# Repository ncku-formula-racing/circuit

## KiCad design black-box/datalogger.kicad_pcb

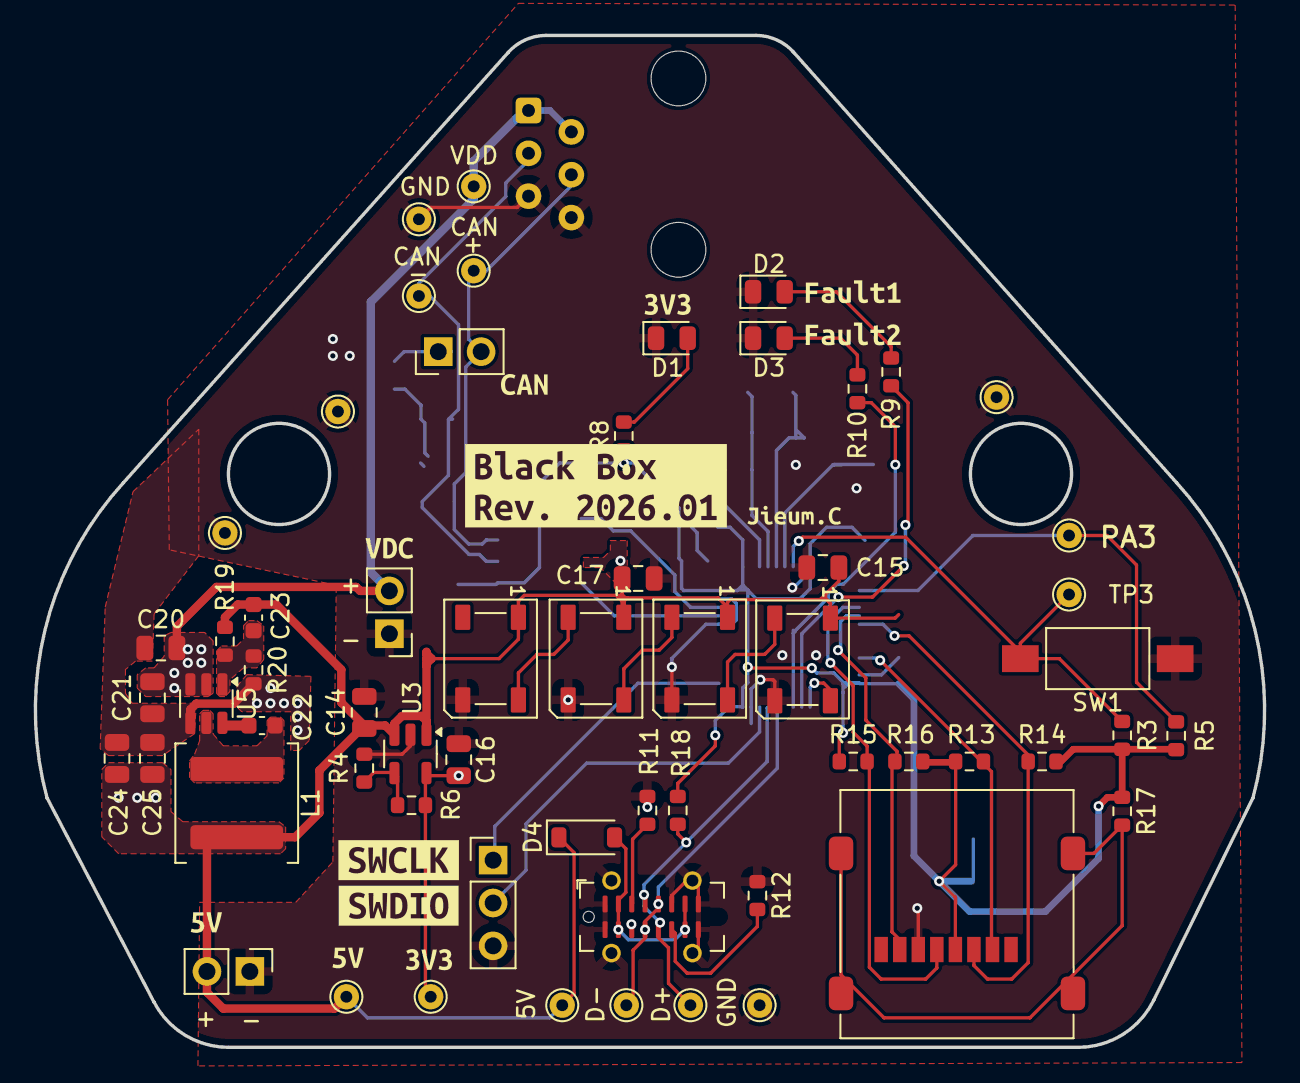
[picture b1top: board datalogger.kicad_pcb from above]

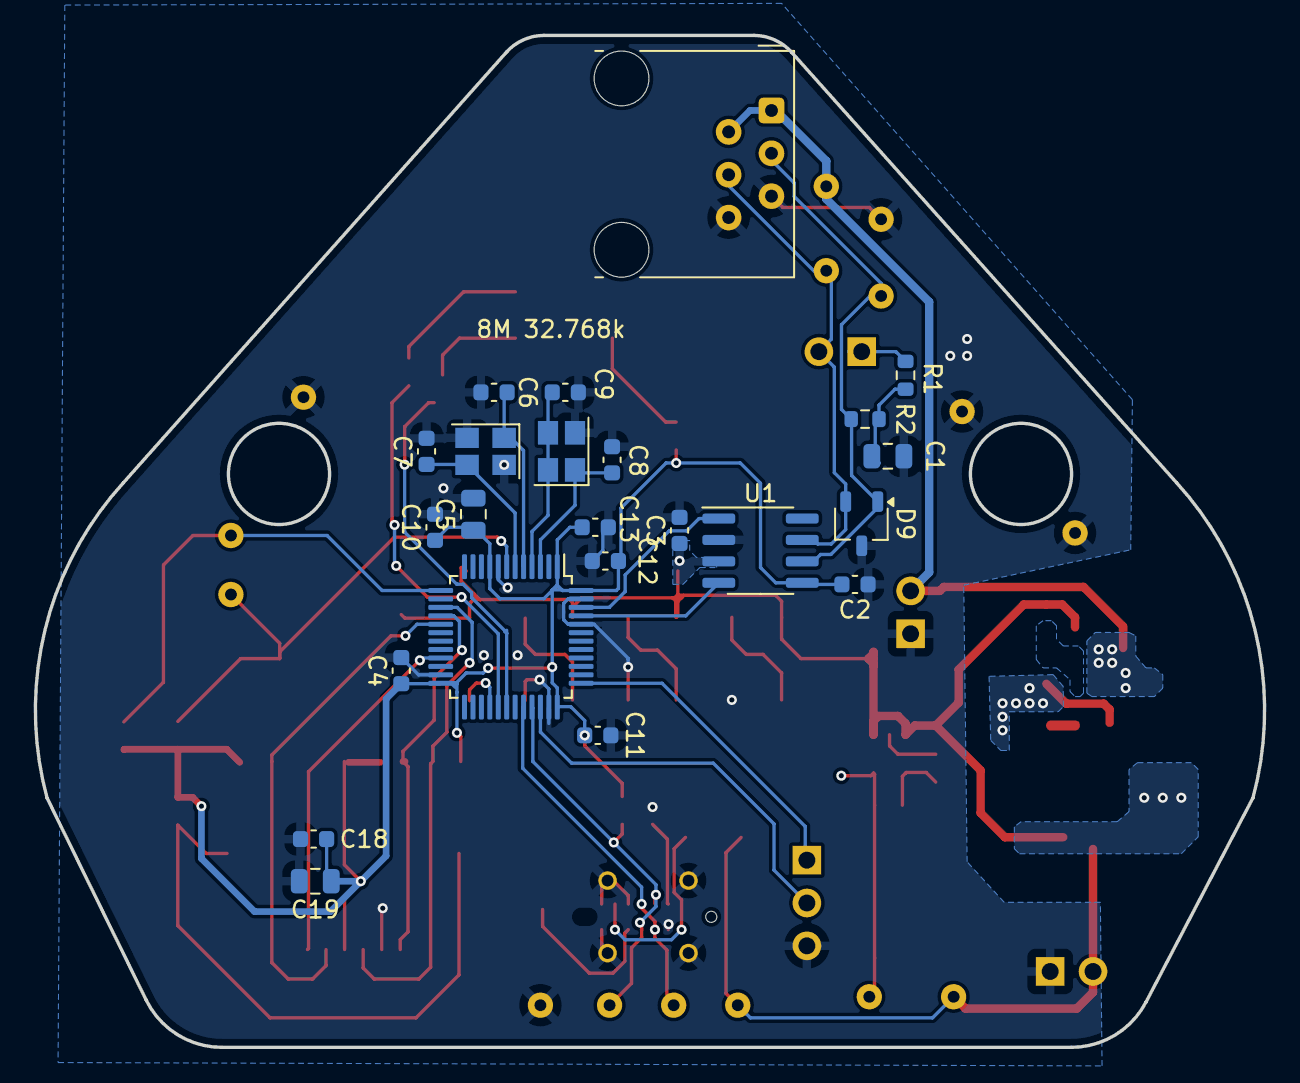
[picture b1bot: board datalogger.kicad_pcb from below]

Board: 2 copper layers, 72.9 x 60.0 mm, 95 parts (23 on the bottom side), 41 nets.

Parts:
5V1: USB_5V; TestPoint_THTPad_D1.5mm_Drill0.7mm
C1, C5, C14, C15, C17, C19: 1u; C_0805_2012Metric
C2, C3, C4, C10, C11, C12, C13, C18, C22: 100n; C_0603_1608Metric
C6, C7, C8, C9: 20p; C_0603_1608Metric
C16, C20, C21: 10u; C_0805_2012Metric
C23: 12p; C_0603_1608Metric
C24, C25: 22u; C_0805_2012Metric
CAN+1: CAN_P; TestPoint_THTPad_D1.5mm_Drill0.7mm
CAN-1: CAN_N; TestPoint_THTPad_D1.5mm_Drill0.7mm
D1, D2, D3: LED; LED_0805_2012Metric
D4: BAT46; D_SOD-123
D5, D6, D7, D8: WS2812B; LED_WS2812B_PLCC4_5.0x5.0mm_P3.2mm
D9: DESD2CAN2SOQ; TSOT-23
D+1: USB_D+; TestPoint_THTPad_D1.5mm_Drill0.7mm
D-1: USB_D-; TestPoint_THTPad_D1.5mm_Drill0.7mm
GND1: GND; TestPoint_THTPad_D1.5mm_Drill0.7mm
GND2: USB_gnd; TestPoint_THTPad_D1.5mm_Drill0.7mm
J1: RJ12; RJ12_Amphenol_54601-x06_Horizontal
J2: PROG; PinHeader_1x03_P2.54mm_Vertical
J3, J6: PWR; PinHeader_1x02_P2.54mm_Vertical
J4: Micro_SD_Card_Det1; microSD_HC_Molex_47219-2001
J5: USB_C_Receptacle_USB2.0_16P; USB_C_Receptacle_G-Switch_GT-USB-7051x
JP1: J_CAN; PinHeader_1x02_P2.54mm_Vertical
L1: 15uH; L_Coilcraft_XAL6060-XXX
R1, R2: 60; R_0603_1608Metric
R3, R5, R8, R9, R10, R13, R14, R15, R16, R17: 10k; R_0603_1608Metric
R4: 100k; R_0603_1608Metric
R6: 166k; R_0603_1608Metric
R11, R12: 5k1; R_0603_1608Metric
R18: 1.5k; R_0603_1608Metric
R19: 534k; R_0603_1608Metric
R20: 30k1; R_0603_1608Metric
SW1: SW_SPST; SW_SPST_FSMSM
TP1: TP_5V; TestPoint_THTPad_D1.5mm_Drill0.7mm
TP2: TP_3V3; TestPoint_THTPad_D1.5mm_Drill0.7mm
TP3: TestPoint; TestPoint_THTPad_D1.5mm_Drill0.7mm
TP11: Shutdown; TestPoint_THTPad_D1.5mm_Drill0.7mm
TP12, TP13, TP14: GND; TestPoint_THTPad_D1.5mm_Drill0.7mm
U1: SN65HVD256D; SOIC-8_3.9x4.9mm_P1.27mm
U2: STM32F103C8Tx; LQFP-48_7x7mm_P0.5mm
U3: AP2204K-ADJ; SOT-23-5
U5: AP63200WU; TSOT-23-6
VDC1: VDD; TestPoint_THTPad_D1.5mm_Drill0.7mm
Y1: 8M; Crystal_SMD_SeikoEpson_FA238-4Pin_3.2x2.5mm
Y2: 32.768k; Crystal_SMD_SeikoEpson_FA238-4Pin_3.2x2.5mm
kibuzzard-6952B1CA: G***; kibuzzard-6952B1CA
kibuzzard-6952B3A2: G***; kibuzzard-6952B3A2
kibuzzard-6952B3D6: G***; kibuzzard-6952B3D6
kibuzzard-6952B4C2: G***; kibuzzard-6952B4C2
kibuzzard-6952B5C0: G***; kibuzzard-6952B5C0
kibuzzard-6952B12B: G***; kibuzzard-6952B12B
kibuzzard-6952B13F: G***; kibuzzard-6952B13F
kibuzzard-6952B17D, kibuzzard-6952B17D#2: G***; kibuzzard-6952B17D
kibuzzard-6952B165, kibuzzard-6952B165#2: G***; kibuzzard-6952B165
kibuzzard-6977A83C: G***; kibuzzard-6977A83C

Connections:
+3V3: C2.1, C4.1, C5.1, C10.1, C11.1, C12.1, C13.1, C16.1, C18.1, C19.1, J4.4 (VDD), R3.1, R5.1, R6.1, R8.1, R13.1, R14.1, R15.1, R16.1, R17.1, R18.1, TP2.1, U1.5 (VRXD), U2.1 (VBAT), U2.9 (VDDA), U2.24 (VDD), U2.36 (VDD), U2.48 (VDD), U3.5 (VOUT)
+5V: 5V1.1, C3.1, C14.1, C15.1, C17.1, C23.1, C24.1, C25.1, D4.1 (K), D5.1 (VDD), D6.1 (VDD), D7.1 (VDD), D8.1 (VDD), J6.2, L1.2, R19.1, TP1.1, U1.3 (VCC), U3.1 (VIN), U3.3 (EN)
/LSE_IN: C8.1, U2.3 (PC14), Y2.1
/LSE_OUT: C9.1, U2.4 (PC15), Y2.3, Y2.4
/RCC_OSC_IN: C6.1, U2.5 (PD0), Y1.1
/RCC_OSC_OUT: C7.1, U2.6 (PD1), Y1.3
CAN_N: CAN-1.1, D9.1 (A1), J1.3, R2.2, U1.6 (CANL)
CAN_P: CAN+1.1, D9.2 (A2), J1.4, JP1.2 (B), U1.7 (CANH)
CRX: U1.4 (RXD), U2.45 (PB8)
CTX: U1.1 (TXD), U2.46 (PB9)
D+: D+1.1, J5.A6 (D+), J5.B6 (D+), R18.2, U2.33 (PA12)
D-: D-1.1, J5.A7 (D-), J5.B7 (D-), U2.32 (PA11)
GND: C1.2, C2.2, C3.2, C4.2, C5.2, C6.2, C7.2, C8.2, C9.2, C10.2, C11.2, C12.2, C13.2, C14.2, C15.2, C16.2, C17.2, C18.2, C19.2, C20.2, C21.2, C24.2, C25.2, D1.1 (K), D2.1 (K), D3.1 (K), D5.3 (VSS), D6.3 (VSS), D7.3 (VSS), D8.3 (VSS), D9.3 (common), GND1.1, GND2.1, J1.5, J1.6, J2.3, J3.1, J4.6 (VSS), J5.A1 (GND), J5.A8 (SBU1), J5.A12 (GND), J5.B1 (GND), J5.B8 (SBU2), J5.B12 (GND), J5.S1 (SHIELD), J6.1, R4.1, R11.1, R12.1, R20.2, SW1.1 (A), TP12.1, TP13.1, TP14.1, U1.2 (GND), U2.8 (VSSA), U2.23 (VSS), U2.35 (VSS), U2.44 (BOOT0), U2.47 (VSS), U3.2 (GND), U5.4 (GND), Y1.2, Y1.4, Y2.2
LED1: R9.1, U2.29 (PA8)
LED2: R10.1, U2.30 (PA9)
NRST: R3.2, SW1.2 (B), TP3.1, U2.7 (NRST)
unnamed: C1.1, R1.2, R2.1
unnamed: D1.2 (A), R8.2
unnamed: D2.2 (A), R9.2
unnamed: D3.2 (A), R10.2
unnamed: D4.2 (A), J5.A4 (VBUS), J5.A9 (VBUS), J5.B4 (VBUS), J5.B9 (VBUS)
unnamed: D5.2 (DOUT), D6.4 (DIN)
unnamed: D6.2 (DOUT), D7.4 (DIN)
unnamed: D7.2 (DOUT), D8.4 (DIN)
unnamed: J4.9 (DET), R17.2
unnamed: J5.A5 (CC1), R11.2
unnamed: J5.B5 (CC2), R12.2
unnamed: JP1.1 (A), R1.1
unnamed: R4.2, R6.2, U3.4 (ADJ)
unnamed: C22.2, U5.6 (BST)
unnamed: C23.2, R19.2, R20.1, U5.1 (FB)
unnamed: C22.1, L1.1, U5.5 (SW)
RGB: D5.4 (DIN), U2.28 (PB15)
SD_CS: J4.2 (DAT3/CD), R13.2, U2.21 (PB10)
SPI1_MISO: J4.7 (DAT0), R16.2, U2.16 (PA6)
SPI1_MOSI: J4.3 (CMD), R14.2, U2.17 (PA7)
SPI1_SCK: J4.5 (CLK), R15.2, U2.15 (PA5)
SWCLK: J2.1, U2.37 (PA14)
SWDIO: J2.2, U2.34 (PA13)
Shutdown: R5.2, TP11.1, U2.13 (PA3)
VDC: C20.1, C21.1, J1.1, J1.2, J3.2, U5.2 (EN), U5.3 (IN), VDC1.1

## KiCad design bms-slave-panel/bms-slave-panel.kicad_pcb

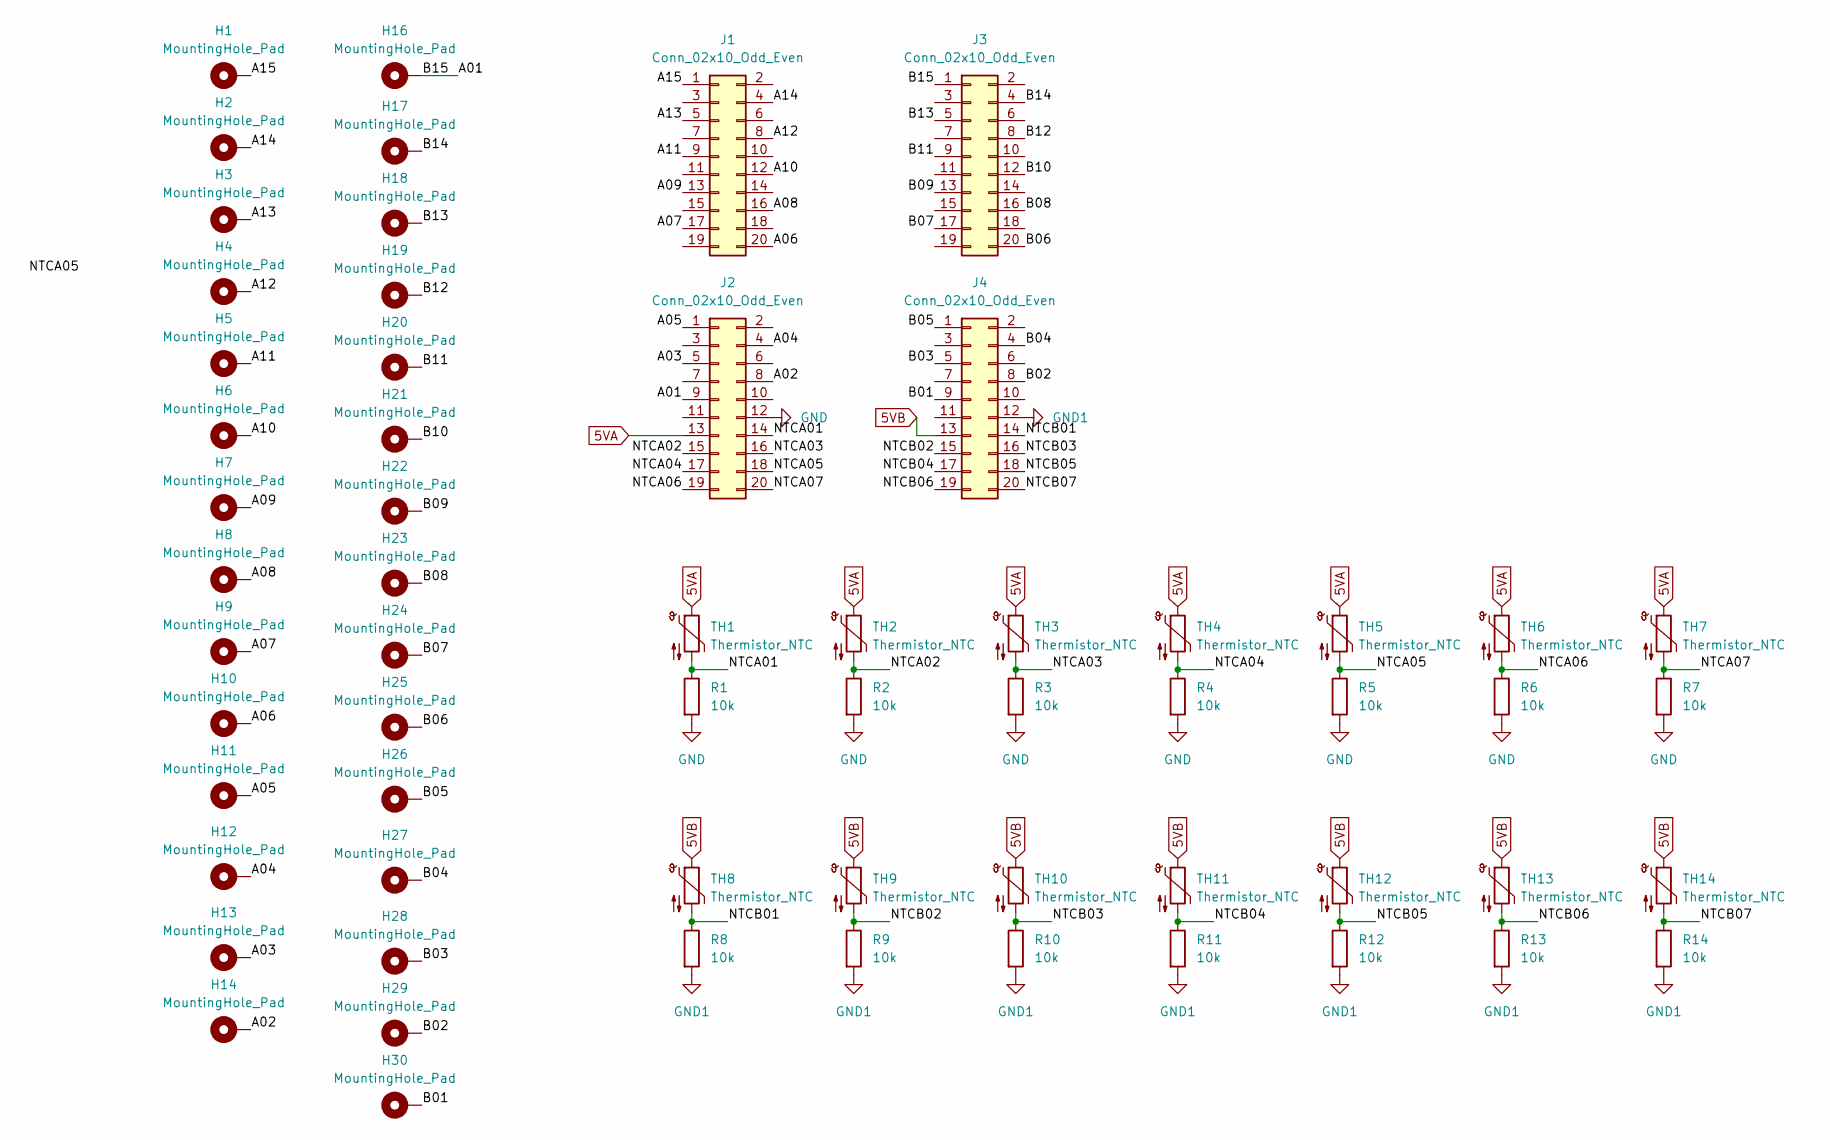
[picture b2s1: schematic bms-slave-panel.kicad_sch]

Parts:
H1, H2, H3, H4, H5, H6, H7, H8, H9, H10, H11, H12, H13, H14, H16, H17, H18, H19, H20, H21, H22, H23, H24, H25, H26, H27, H28, H29, H30: MountingHole_Pad; MountingHole_4.3mm_M4_DIN965_Pad
J1, J2, J3, J4: Conn_02x10_Odd_Even; PinHeader_2x10_P2.54mm_Vertical_SMD
R1, R2, R3, R4, R5, R6, R7, R8, R9, R10, R11, R12, R13, R14: 10k; R_0805_2012Metric
TH1, TH2, TH3, TH4, TH5, TH6, TH7, TH8, TH9, TH10, TH11, TH12, TH13, TH14: Thermistor_NTC; R_0805_2012Metric

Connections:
5VA: J2.13, TH1.1, TH2.1, TH3.1, TH4.1, TH5.1, TH6.1, TH7.1
5VB: J4.13, TH8.1, TH9.1, TH10.1, TH11.1, TH12.1, TH13.1, TH14.1
/A01: H16.1, J2.9, J3.1
/A02: H14.1, J2.8
/A03: H13.1, J2.5
/A04: H12.1, J2.4
/A05: H11.1, J2.1
/A06: H10.1, J1.20
/A07: H9.1, J1.17
/A08: H8.1, J1.16
/A09: H7.1, J1.13
/A10: H6.1, J1.12
/A11: H5.1, J1.9
/A12: H4.1, J1.8
/A13: H3.1, J1.5
/A14: H2.1, J1.4
/A15: H1.1, J1.1
/B01: H30.1, J4.9
/B02: H29.1, J4.8
/B03: H28.1, J4.5
/B04: H27.1, J4.4
/B05: H26.1, J4.1
/B06: H25.1, J3.20
/B07: H24.1, J3.17
/B08: H23.1, J3.16
/B09: H22.1, J3.13
/B10: H21.1, J3.12
/B11: H20.1, J3.9
/B12: H19.1, J3.8
/B13: H18.1, J3.5
/B14: H17.1, J3.4
/NTCA01: J2.14, R1.1, TH1.2
/NTCA02: J2.15, R2.1, TH2.2
/NTCA03: J2.16, R3.1, TH3.2
/NTCA04: J2.17, R4.1, TH4.2
/NTCA05: J2.18, R5.1, TH5.2
/NTCA06: J2.19, R6.1, TH6.2
/NTCA07: J2.20, R7.1, TH7.2
/NTCB01: J4.14, R8.1, TH8.2
/NTCB02: J4.15, R9.1, TH9.2
/NTCB03: J4.16, R10.1, TH10.2
/NTCB04: J4.17, R11.1, TH11.2
/NTCB05: J4.18, R12.1, TH12.2
/NTCB06: J4.19, R13.1, TH13.2
/NTCB07: J4.20, R14.1, TH14.2
GND: J2.12, R1.2, R2.2, R3.2, R4.2, R5.2, R6.2, R7.2
GND1: J4.12, R8.2, R9.2, R10.2, R11.2, R12.2, R13.2, R14.2

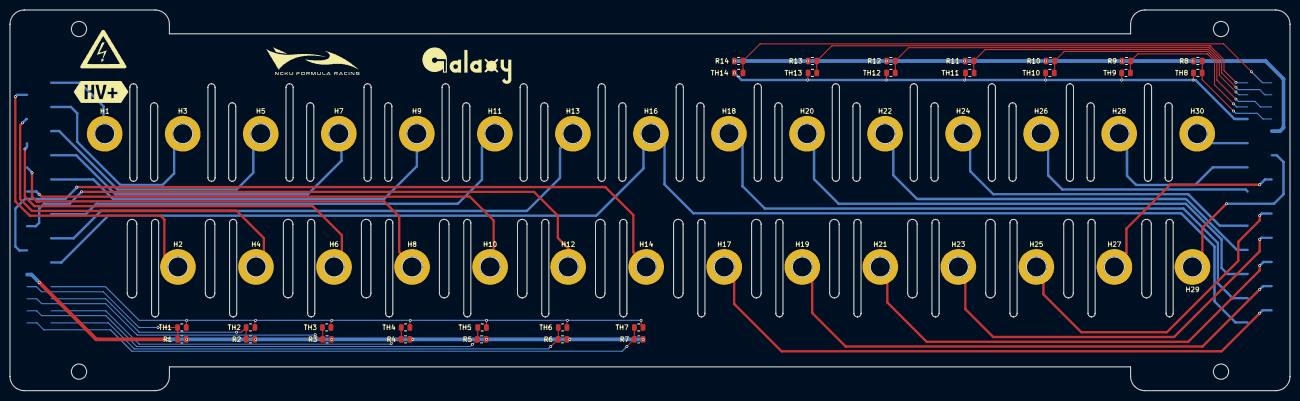
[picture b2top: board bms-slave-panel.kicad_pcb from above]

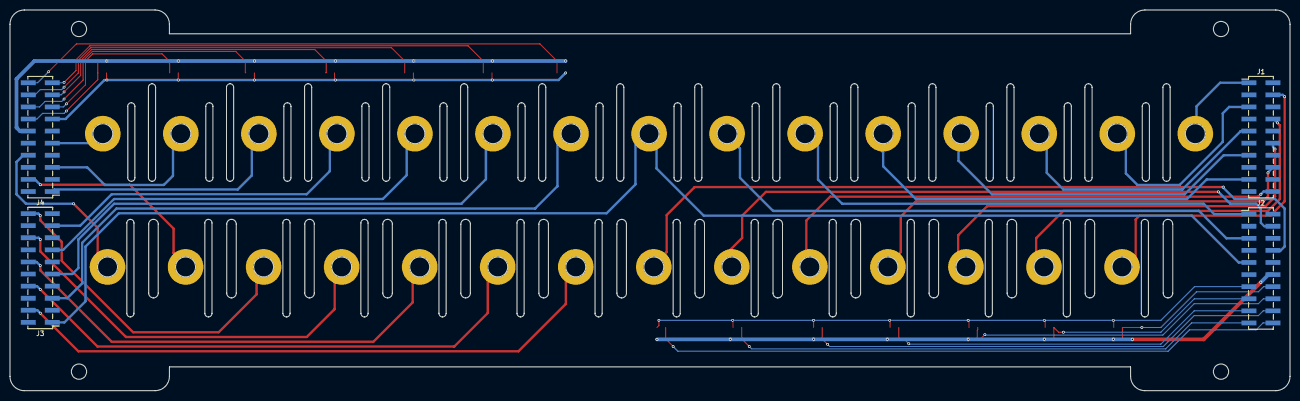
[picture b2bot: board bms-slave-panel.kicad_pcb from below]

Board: 2 copper layers, 269.0 x 80.0 mm, 62 parts (4 on the bottom side), 47 nets.

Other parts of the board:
kibuzzard-69D53A8A: G***; kibuzzard-69D53A8A

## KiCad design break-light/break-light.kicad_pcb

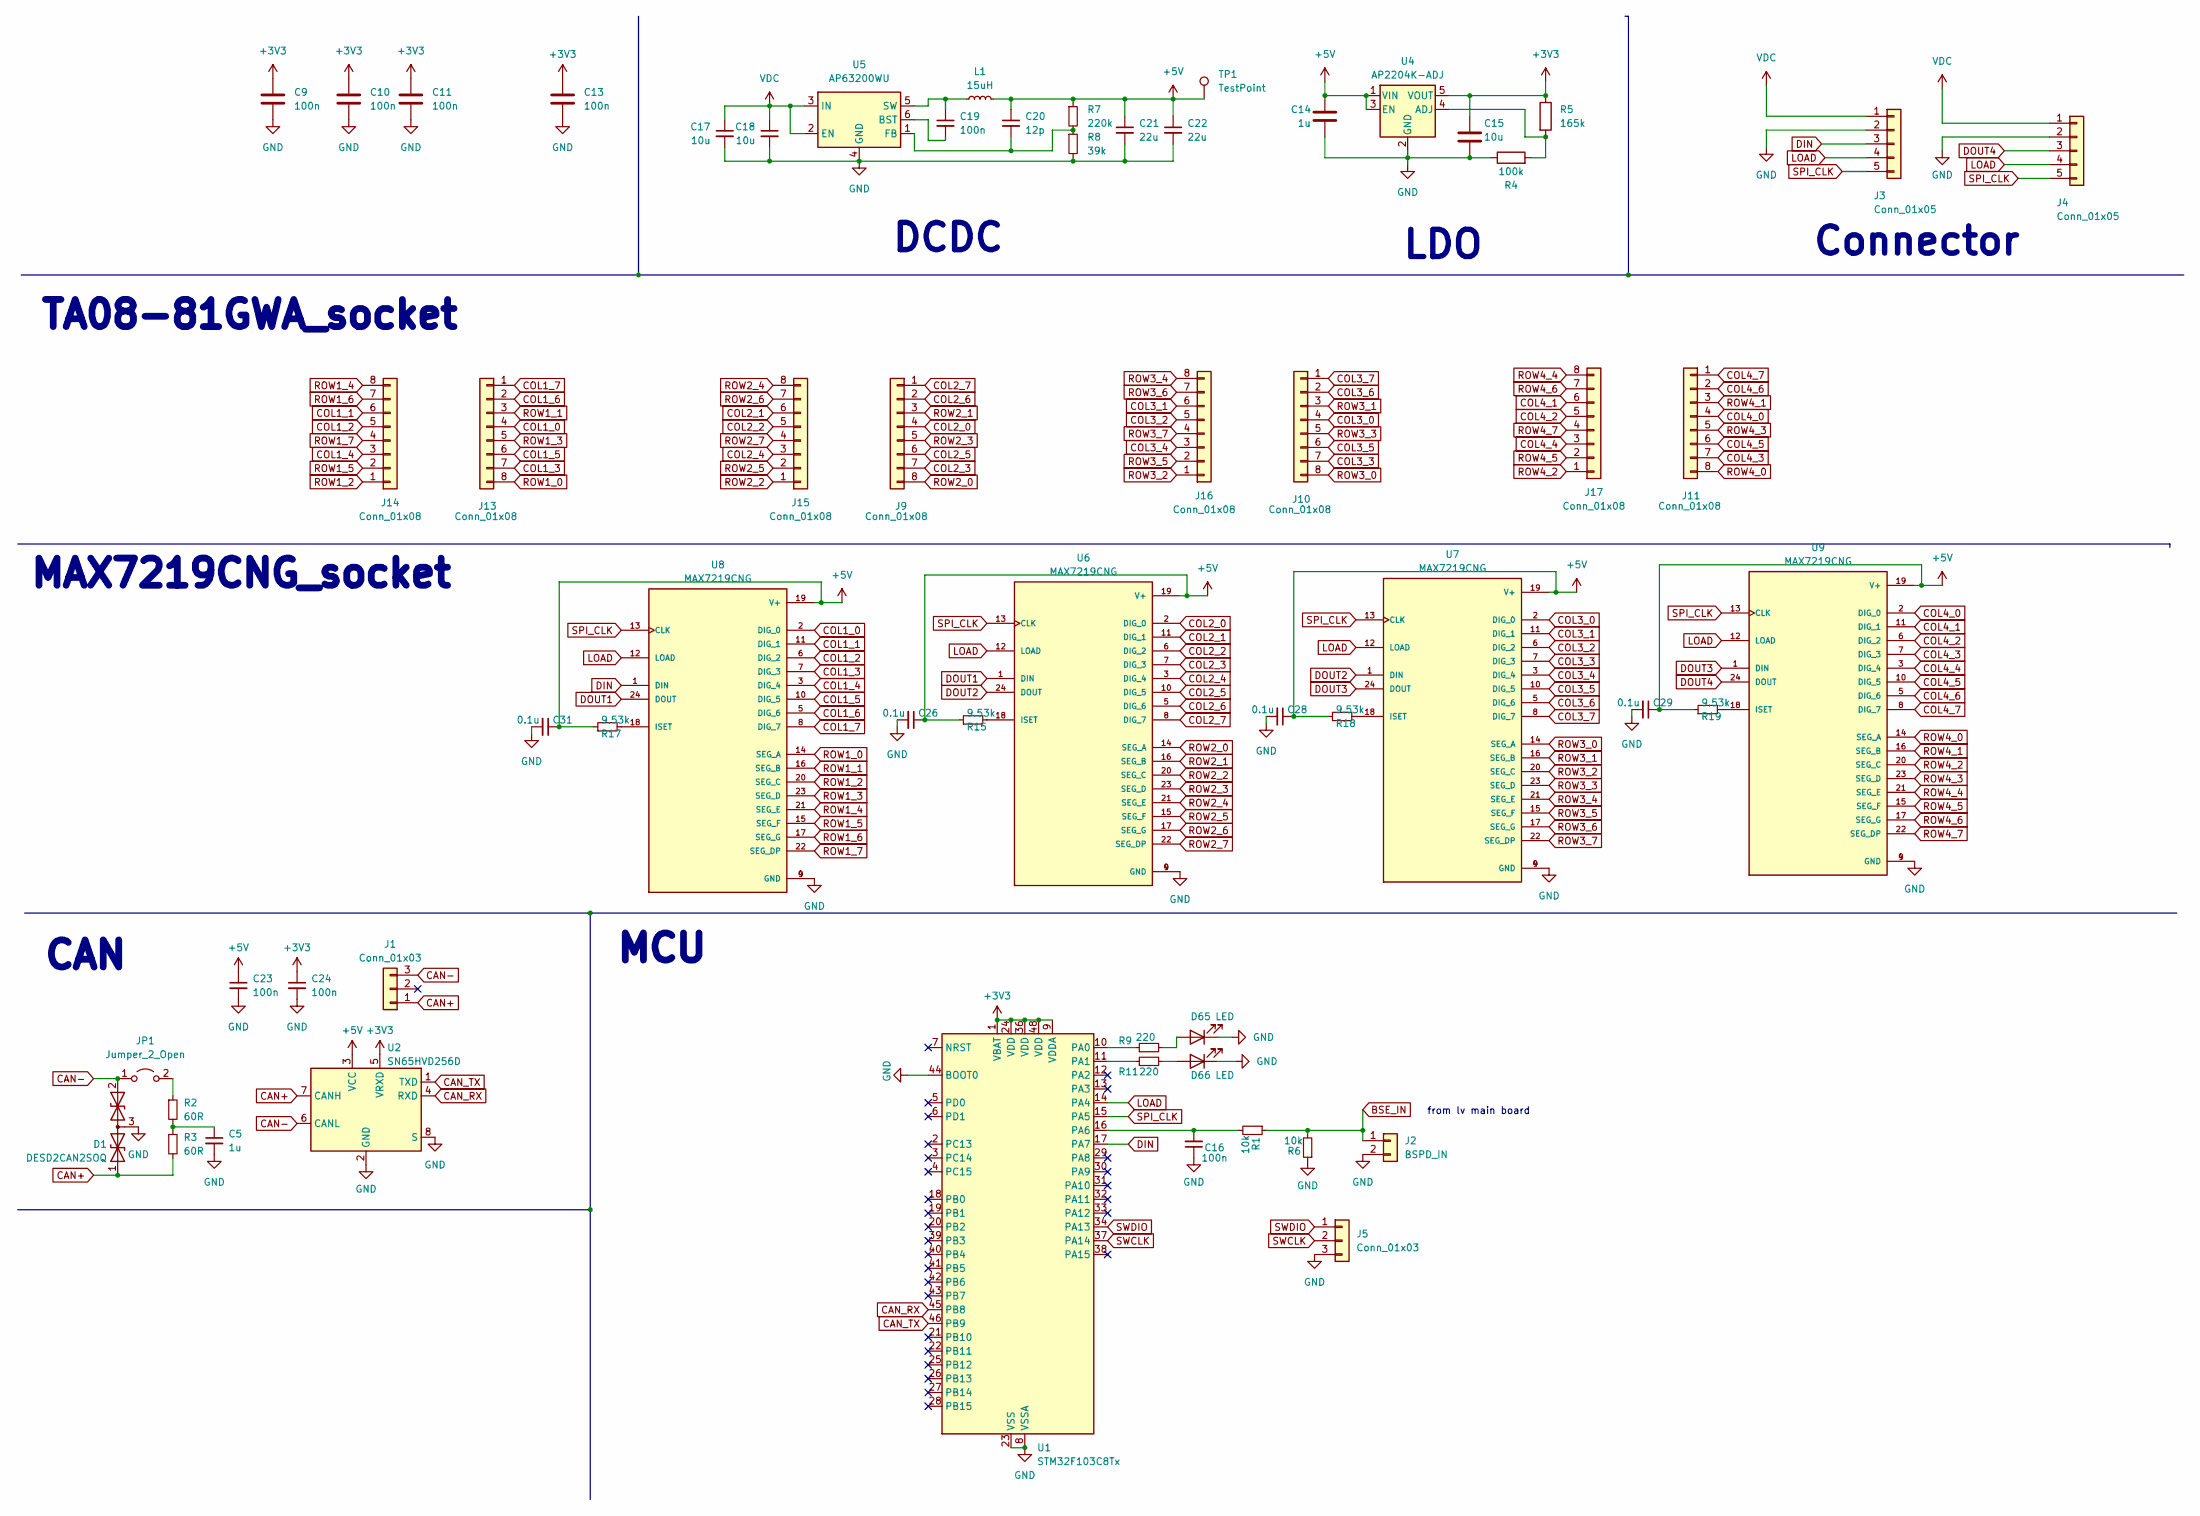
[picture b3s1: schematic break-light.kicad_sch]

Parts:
C5: 1u; C_0603_1608Metric
C9, C10, C11, C13: 100n; R_0603_1608Metric
C14: 1u; R_0603_1608Metric
C15: 10u; R_0805_2012Metric
C16, C19, C23, C24: 100n; C_0603_1608Metric
C17, C18: 10u; C_0805_2012Metric
C20: 12p; C_0603_1608Metric
C21, C22: 22u; C_0805_2012Metric
C26, C28, C29, C31: 0.1u; C_0603_1608Metric
D1: DESD2CAN2SOQ; TSOT-23
D65, D66: LED; LED_0805_2012Metric
J1, J5: Conn_01x03; PinHeader_1x03_P2.54mm_Vertical
J2: BSPD_IN; JST_XH_B2B-XH-A_1x02_P2.50mm_Vertical
J3, J4: Conn_01x05; PinHeader_1x05_P2.54mm_Vertical
J9, J10, J11, J13, J14, J15, J16, J17: Conn_01x08; PinSocket_1x08_P2.54mm_Vertical
JP1: Jumper_2_Open; PinHeader_1x02_P2.54mm_Vertical
L1: 15uH; L_Coilcraft_XAL6060-XXX
R1, R6: 10k; R_0603_1608Metric
R2, R3: 60R; R_0603_1608Metric
R4: 100k; R_0603_1608Metric
R5: 165k; R_0603_1608Metric
R7: 220k; R_0603_1608Metric
R8: 39k; R_0603_1608Metric
R9, R11: 220; R_0603_1608Metric
R15, R17, R18, R19: 9.53k; R_0603_1608Metric
TP1: TestPoint; TestPoint_THTPad_D1.5mm_Drill0.7mm
U1: STM32F103C8Tx; LQFP-48_7x7mm_P0.5mm
U2: SN65HVD256D; SOIC-8_3.9x4.9mm_P1.27mm
U4: AP2204K-ADJ; SOT-23-5
U5: AP63200WU; TSOT-23-6
U6, U7, U8, U9: MAX7219CNG; DIP-24_W7.62mm_Socket; PARTREV 6

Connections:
+3V3: C9.1, C10.1, C11.1, C13.1, C15.1, C24.1, R5.1, U1.1 (VBAT), U1.9 (VDDA), U1.24 (VDD), U1.36 (VDD), U1.48 (VDD), U2.5 (VRXD), U4.5 (VOUT)
+5V: C14.1, C20.1, C21.1, C22.1, C23.1, C26.1, C28.1, C29.1, C31.1, L1.2, R7.1, R15.1, R17.1, R18.1, R19.1, TP1.1, U2.3 (VCC), U4.1 (VIN), U4.3 (EN), U6.19 (V+), U7.19 (V+), U8.19 (V+), U9.19 (V+)
BSE_IN: J2.1, R1.1, R6.2
CAN+: D1.1 (A1), J1.1, R3.2, U2.7 (CANH)
CAN-: D1.2 (A2), J1.3, JP1.1 (A), U2.6 (CANL)
CAN_RX: U1.45 (PB8), U2.4 (RXD)
CAN_TX: U1.46 (PB9), U2.1 (TXD)
COL1_0: J13.4, U8.2 (DIG_0)
COL1_1: J14.6, U8.11 (DIG_1)
COL1_2: J14.5, U8.6 (DIG_2)
COL1_3: J13.7, U8.7 (DIG_3)
COL1_4: J14.3, U8.3 (DIG_4)
COL1_5: J13.6, U8.10 (DIG_5)
COL1_6: J13.2, U8.5 (DIG_6)
COL1_7: J13.1, U8.8 (DIG_7)
COL2_0: J9.4, U6.2 (DIG_0)
COL2_1: J15.6, U6.11 (DIG_1)
COL2_2: J15.5, U6.6 (DIG_2)
COL2_3: J9.7, U6.7 (DIG_3)
COL2_4: J15.3, U6.3 (DIG_4)
COL2_5: J9.6, U6.10 (DIG_5)
COL2_6: J9.2, U6.5 (DIG_6)
COL2_7: J9.1, U6.8 (DIG_7)
COL3_0: J10.4, U7.2 (DIG_0)
COL3_1: J16.6, U7.11 (DIG_1)
COL3_2: J16.5, U7.6 (DIG_2)
COL3_3: J10.7, U7.7 (DIG_3)
COL3_4: J16.3, U7.3 (DIG_4)
COL3_5: J10.6, U7.10 (DIG_5)
COL3_6: J10.2, U7.5 (DIG_6)
COL3_7: J10.1, U7.8 (DIG_7)
COL4_0: J11.4, U9.2 (DIG_0)
COL4_1: J17.6, U9.11 (DIG_1)
COL4_2: J17.5, U9.6 (DIG_2)
COL4_3: J11.7, U9.7 (DIG_3)
COL4_4: J17.3, U9.3 (DIG_4)
COL4_5: J11.6, U9.10 (DIG_5)
COL4_6: J11.2, U9.5 (DIG_6)
COL4_7: J11.1, U9.8 (DIG_7)
DIN: J3.3, U1.17 (PA7), U8.1 (DIN)
DOUT1: U6.1 (DIN), U8.24 (DOUT)
DOUT2: U6.24 (DOUT), U7.1 (DIN)
DOUT3: U7.24 (DOUT), U9.1 (DIN)
DOUT4: J4.3, U9.24 (DOUT)
GND: C5.2, C9.2, C10.2, C11.2, C13.2, C14.2, C15.2, C16.1, C17.2, C18.2, C21.2, C22.2, C23.2, C24.2, C26.2, C28.2, C29.2, C31.2, D1.3 (common), D65.1 (K), D66.1 (K), J2.2, J3.2, J4.2, J5.3, R4.1, R6.1, R8.2, U1.8 (VSSA), U1.23 (VSS), U1.35 (VSS), U1.44 (BOOT0), U1.47 (VSS), U2.2 (GND), U2.8 (S), U4.2 (GND), U5.4 (GND), U6.4 (GND), U6.9 (GND), U7.4 (GND), U7.9 (GND), U8.4 (GND), U8.9 (GND), U9.4 (GND), U9.9 (GND)
LOAD: J3.4, J4.4, U1.14 (PA4), U6.12 (LOAD), U7.12 (LOAD), U8.12 (LOAD), U9.12 (LOAD)
unnamed: C5.1, R2.2, R3.1
unnamed: D65.2 (A), R9.2
unnamed: D66.2 (A), R11.2
unnamed: JP1.2 (B), R2.1
unnamed: R9.1, U1.10 (PA0)
unnamed: R11.1, U1.11 (PA1)
unnamed: C16.2, R1.2, U1.16 (PA6)
unnamed: R4.2, R5.2, U4.4 (ADJ)
unnamed: C19.2, U5.6 (BST)
unnamed: C20.2, R7.2, R8.1, U5.1 (FB)
unnamed: C19.1, L1.1, U5.5 (SW)
unnamed: R15.2, U6.18 (ISET)
unnamed: R18.2, U7.18 (ISET)
unnamed: R17.2, U8.18 (ISET)
unnamed: R19.2, U9.18 (ISET)
ROW1_0: J13.8, U8.14 (SEG_A)
ROW1_1: J13.3, U8.16 (SEG_B)
ROW1_2: J14.1, U8.20 (SEG_C)
ROW1_3: J13.5, U8.23 (SEG_D)
ROW1_4: J14.8, U8.21 (SEG_E)
ROW1_5: J14.2, U8.15 (SEG_F)
ROW1_6: J14.7, U8.17 (SEG_G)
ROW1_7: J14.4, U8.22 (SEG_DP)
ROW2_0: J9.8, U6.14 (SEG_A)
ROW2_1: J9.3, U6.16 (SEG_B)
ROW2_2: J15.1, U6.20 (SEG_C)
ROW2_3: J9.5, U6.23 (SEG_D)
ROW2_4: J15.8, U6.21 (SEG_E)
ROW2_5: J15.2, U6.15 (SEG_F)
ROW2_6: J15.7, U6.17 (SEG_G)
ROW2_7: J15.4, U6.22 (SEG_DP)
ROW3_0: J10.8, U7.14 (SEG_A)
ROW3_1: J10.3, U7.16 (SEG_B)
ROW3_2: J16.1, U7.20 (SEG_C)
ROW3_3: J10.5, U7.23 (SEG_D)
ROW3_4: J16.8, U7.21 (SEG_E)
ROW3_5: J16.2, U7.15 (SEG_F)
ROW3_6: J16.7, U7.17 (SEG_G)
ROW3_7: J16.4, U7.22 (SEG_DP)
ROW4_0: J11.8, U9.14 (SEG_A)
ROW4_1: J11.3, U9.16 (SEG_B)
ROW4_2: J17.1, U9.20 (SEG_C)
ROW4_3: J11.5, U9.23 (SEG_D)
ROW4_4: J17.8, U9.21 (SEG_E)
ROW4_5: J17.2, U9.15 (SEG_F)
ROW4_6: J17.7, U9.17 (SEG_G)
ROW4_7: J17.4, U9.22 (SEG_DP)
SPI_CLK: J3.5, J4.5, U1.15 (PA5), U6.13 (CLK), U7.13 (CLK), U8.13 (CLK), U9.13 (CLK)
SWCLK: J5.2, U1.37 (PA14)
SWDIO: J5.1, U1.34 (PA13)
VDC: C17.1, C18.1, J3.1, J4.1, U5.2 (EN), U5.3 (IN)

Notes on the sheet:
Connector
from lv main board
CAN
MAX7219CNG_socket
DCDC
TA08-81GWA_socket
LDO
MCU

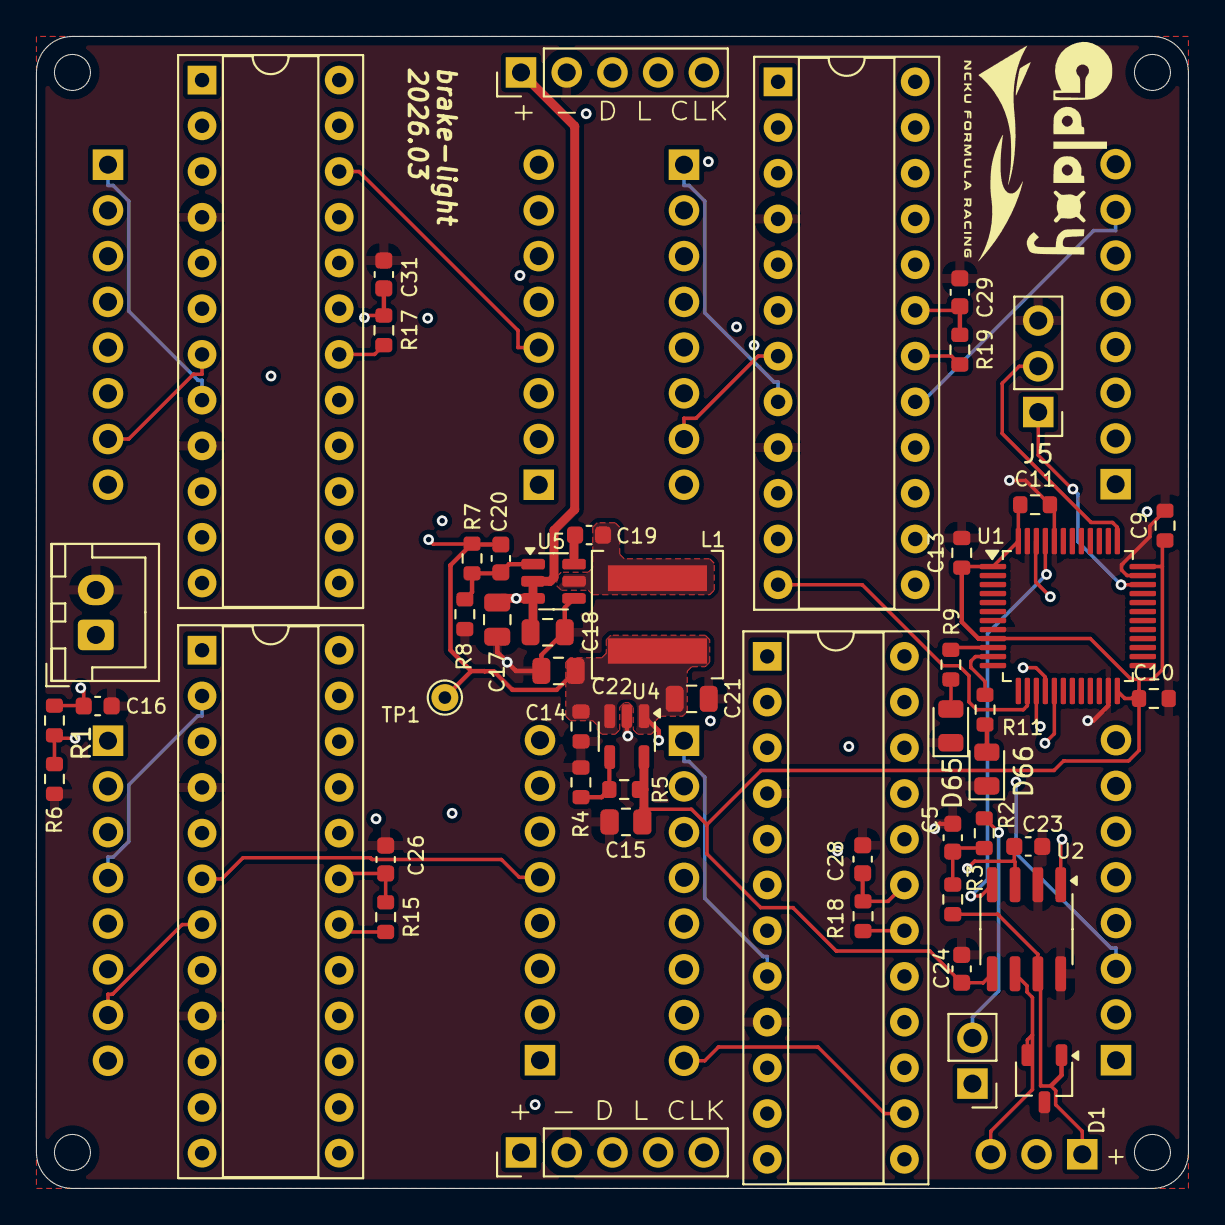
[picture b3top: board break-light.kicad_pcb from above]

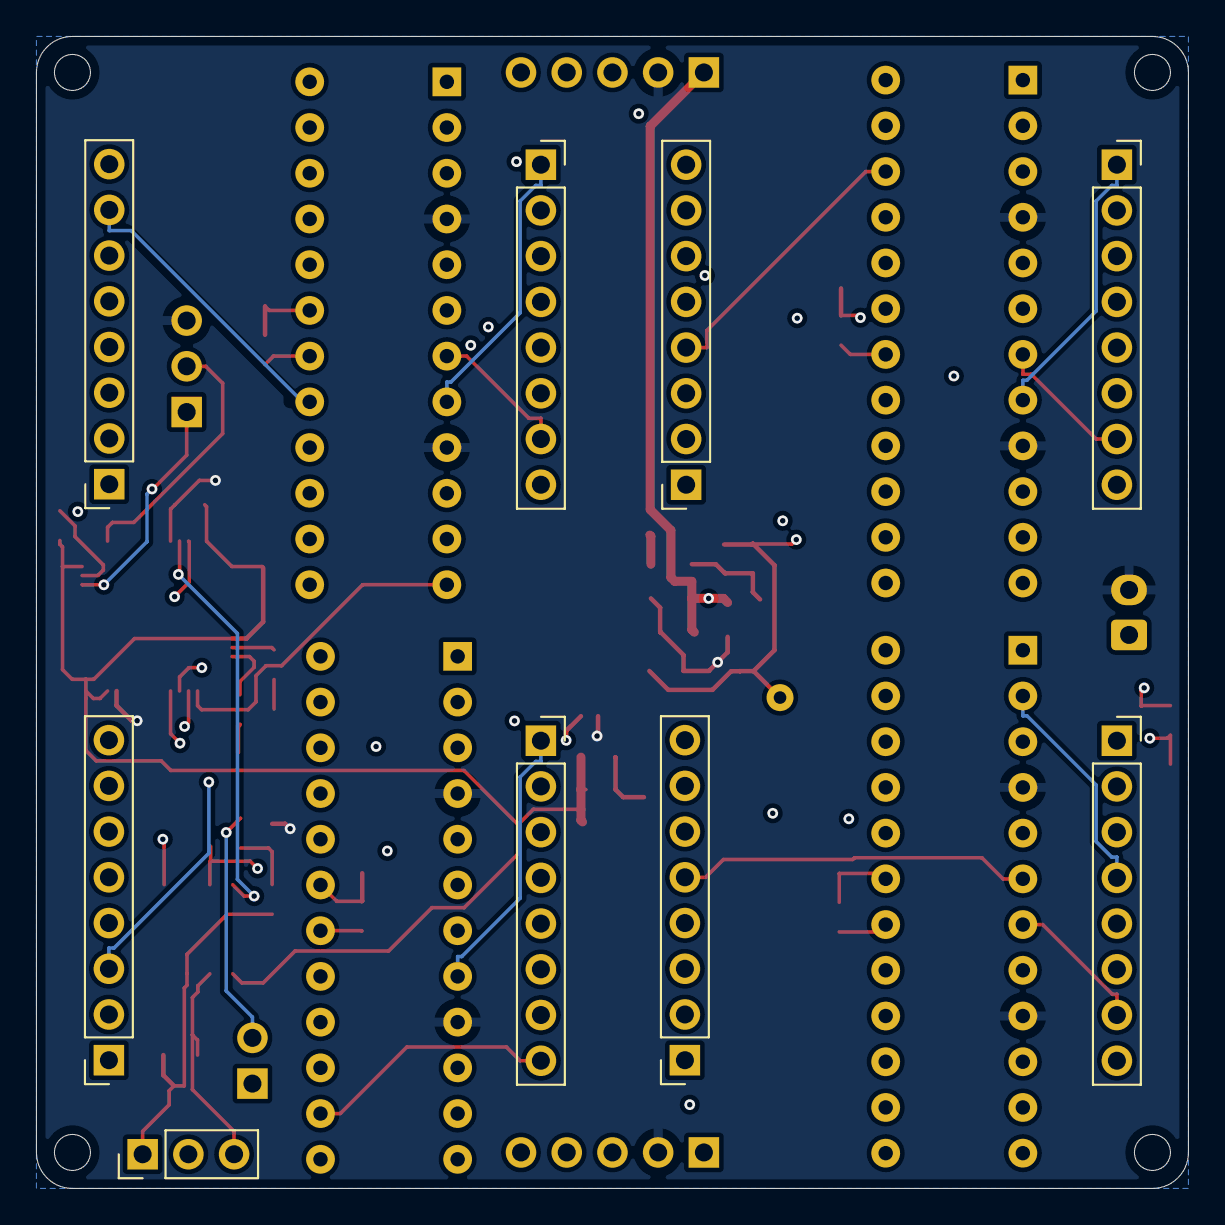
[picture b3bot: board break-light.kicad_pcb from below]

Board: 4 copper layers, 64.0 x 64.0 mm, 63 parts (9 on the bottom side), 97 nets.

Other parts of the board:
G1, G2: LOGO
